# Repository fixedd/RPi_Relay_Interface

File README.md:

# Raspberry Pi Relay Module Interface Board

## Note / Warning

This was formerly stated to be for the SainSmart relay modules, but it was later pointed out to me that these boards actually already have this logic built in to them. 

## Overview

These interface boards will allow you to connect your [Raspberry Pi](http://www.amazon.com/gp/product/B009SQQF9C/ref=as_li_ss_tl?ie=UTF8&camp=1789&creative=390957&creativeASIN=B009SQQF9C&linkCode=as2&tag=fixedd-20) (rev 2.0, at least) to a 4 or 8-Channel 5V Relay Module.

## Parts List
### 8-Channel 5V Relay Module

| Quantity | Part                             | Notes |
| :------: | -------------------------------- | ----- |
| 8        | 12kΩ ¼ Watt Resistors            | [This multi-pack](http://www.amazon.com/gp/product/B003UC4FSS/ref=as_li_ss_tl?ie=UTF8&camp=1789&creative=390957&creativeASIN=B003UC4FSS&linkCode=as2&tag=fixedd-20) has all the resistors you'll need for this, and much more. |
| 8        | 10kΩ ¼ Watt Resistors            |       |
| 8        | 2N3904 Transistors               | [Amazon](http://www.amazon.com/gp/product/B00AUEFGU0/ref=as_li_ss_tl?ie=UTF8&camp=1789&creative=390957&creativeASIN=B00AUEFGU0&linkCode=as2&tag=fixedd-20). |
| 1        | 2 inch x 2 inch single-sided PCB | I cut [this](http://www.amazon.com/gp/product/B000P7ALZC/ref=as_li_ss_tl?ie=UTF8&camp=1789&creative=390957&creativeASIN=B000P7ALZC&linkCode=as2&tag=fixedd-20) down. |
| 1        | 3 inch jumper wire               |       |
| 1        | 26 pin header (2x13)             | [This] will be more than enough. |
| 1        | 10 pin header (1x10)             |       |

### 4-Channel 5V Relay Module
| Quantity | Part                             | Notes |
| :------: | -------------------------------- | ----- |
| 4        | 12kΩ ¼ Watt Resistors            | [This multi-pack](http://www.amazon.com/gp/product/B003UC4FSS/ref=as_li_ss_tl?ie=UTF8&camp=1789&creative=390957&creativeASIN=B003UC4FSS&linkCode=as2&tag=fixedd-20) has all the resistors you'll need for this, and much more. |
| 4        | 10kΩ ¼ Watt Resistors            |       |
| 4        | 2N3904 Transistors               | [Amazon](http://www.amazon.com/gp/product/B00AUEFGU0/ref=as_li_ss_tl?ie=UTF8&camp=1789&creative=390957&creativeASIN=B00AUEFGU0&linkCode=as2&tag=fixedd-20). |
| 1        | 2 inch x 2 inch single-sided PCB | I cut [this](http://www.amazon.com/gp/product/B000P7ALZC/ref=as_li_ss_tl?ie=UTF8&camp=1789&creative=390957&creativeASIN=B000P7ALZC&linkCode=as2&tag=fixedd-20) down. |
| 1        | 3 inch jumper wire               |       |
| 1        | 26 pin header (2x13)             | [This] will be more than enough. |
| 1        | 10 pin header (1x10)             |       |

## Explanation

The relay boards are powered by 5v and the relays are triggered by taking the input pin to ground. Since the Raspberry Pi's GPIO pins output 3.3v I used a set of transistors to take the relay pins to ground.

I used 2N3904 transistors simply because they were cheap and readily available. In theory any NPN transistor should work, but the resistors may need to be adjusted.

To make the board I used the toner transfer method. There are [plenty of instructions](http://www.instructables.com/id/Cheap-and-Easy-Toner-Transfer-for-PCB-Making/) on the internet for this, so I won't go into it here.

The Relay Module I used has opto-isolation on the input pins. To maintain this isolation you would need to use an external 5v power supply instead of using the Pi's.

### Files

* ```eagle_files``` - Provided here are [Eagle PCB](http://www.cadsoftusa.com/eagle-pcb-design-software/) schematic and layout files.
* ```gerber_files``` - these are [Gerber format](http://en.wikipedia.org/wiki/Gerber_format) files so it will be easy to have boards manufactured.
* ```images``` - Images of my board and the files I printed to do the toner transfer.
* ```test_scripts``` - Some python scripts to test the operation of the board.

## Video

## Thanks

* Thanks to the folks on the [Raspberry Pi BB](http://www.raspberrypi.org/phpBB3/viewtopic.php?t=19222), without their guidance it would have taken me longer to figure this out.
* Thanks to @lazylester for the Gerber files for the 8-channel version.
* Thanks to @fjung for the Eagle and Gerber files for the 4-channel version.

## License

There is no license other than to say that I release this to the public domain... do with it as you wish (see [the license file](./LICENSE.md)).

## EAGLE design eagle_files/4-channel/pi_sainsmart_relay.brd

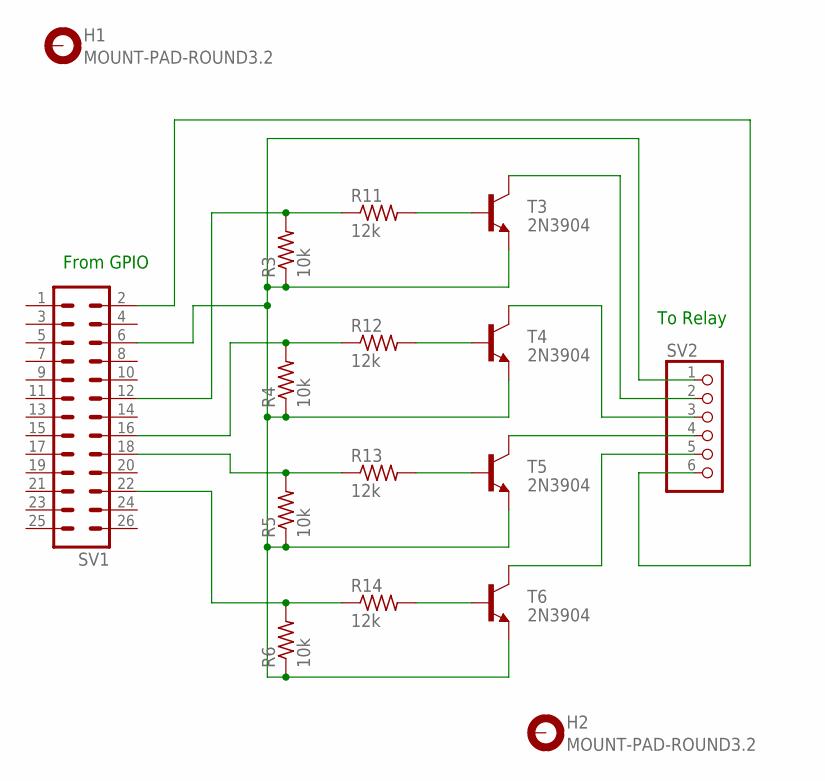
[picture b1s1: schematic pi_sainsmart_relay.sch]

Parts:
H1, H2: MOUNT-PAD-ROUND3.2; 3,2-PAD
R3, R4, R5, R6: 10k; 0204V
R11, R12, R13, R14: 12k; 0207/12
SV1: MA13-2
SV2: PINHD-1X6; 1X06
T3, T4, T5, T6: 2N3904; TO92-EBC

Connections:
GND: R3.1, R4.1, R5.1, R6.1, SV1.6, SV2.1, T3.E, T4.E, T5.E, T6.E
unnamed: SV1.2, SV2.6
unnamed: R14.2, T6.B
unnamed: R13.2, T5.B
unnamed: R12.2, T4.B
unnamed: R11.2, T3.B
unnamed: SV2.2, T3.C
unnamed: SV2.3, T4.C
unnamed: SV2.4, T5.C
unnamed: SV2.5, T6.C
unnamed: R3.2, R11.1, SV1.12
unnamed: R4.2, R12.1, SV1.16
unnamed: R5.2, R13.1, SV1.18
unnamed: R6.2, R14.1, SV1.22

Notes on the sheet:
To Relay
From GPIO

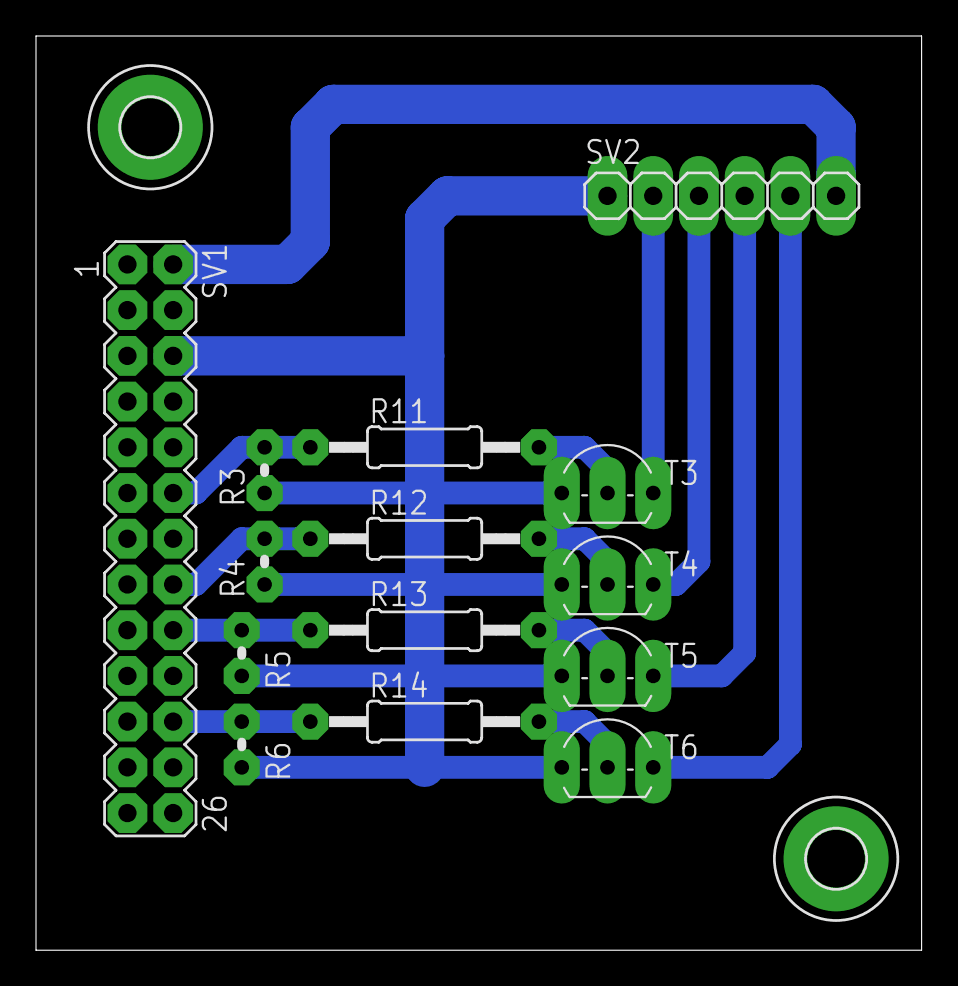
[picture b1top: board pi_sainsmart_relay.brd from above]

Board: 2 copper layers, 49.2 x 50.8 mm, 16 parts (0 on the bottom side), 14 nets.

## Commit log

2013-03-27 Added headers to parts list.
2013-03-27 Clarified header descriptions.
2013-07-06 adds gerber files
2013-08-09 Added description of gerber_files directory to README.
2013-10-07 Update README.md
    mentioning the (lack of a) license in the readme
2014-02-22 added Sainsmart 4-Channel 5V Relay Module
2014-02-22 Removing references to SainSmart
2014-02-22 updated parts lists
2014-02-22 trying to organize 4-channel vs 8-channel
2014-02-22 Adding in contributors.
